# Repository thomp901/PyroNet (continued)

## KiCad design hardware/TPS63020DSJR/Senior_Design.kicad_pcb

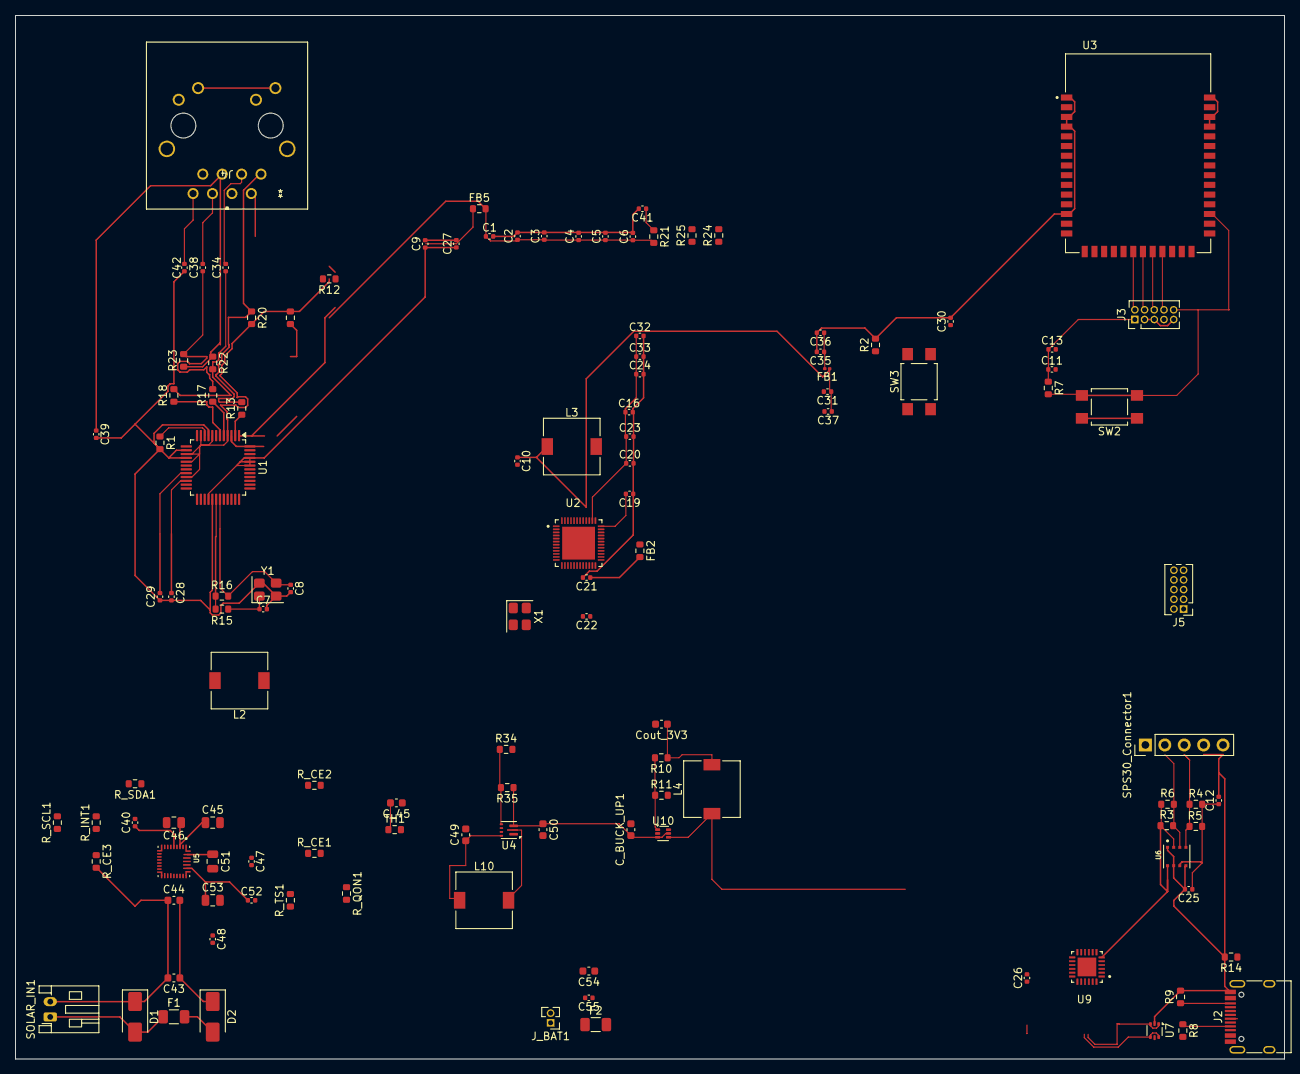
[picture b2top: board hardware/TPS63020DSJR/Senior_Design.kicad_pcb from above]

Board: 2 copper layers, 166.0 x 136.5 mm, 121 parts (0 on the bottom side), 85 nets.

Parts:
C1, C2, C3, C4, C5, C9, C24, C31, C32, C52: 0.1uF; C_0402_1005Metric
C6, C27: 10uF/16V; C_0402_1005Metric
C7, C8: 18pF; C_0402_1005Metric
C10, C26, C29: 4.7uF; C_0402_1005Metric
C11, C12, C21, C25, C30, C36: 100nF; C_0402_1005Metric
C13: 100uF; C_0402_1005Metric
C16: 10uF; C_0402_1005Metric
C19, C23, C33, C37, C40: 1uF; C_0402_1005Metric
C20, C28, C39: 10nF; C_0402_1005Metric
C22, C35: 120pF; C_0402_1005Metric
C34, C38: 6.8nF; C_0402_1005Metric
C41: 22nF; C_0402_1005Metric
C42: 1nF/2kV; C_0402_1005Metric
C43, C49: 10uF; C_0603_1608Metric
C44: 0.1uF; C_0603_1608Metric
C45, C51: 10uF; C_0805_2012Metric
C46: 0.1uF; C_0805_2012Metric
C47, C48: 47 nF; C_0402_1005Metric
C50: 22uF; C_0603_1608Metric
C53: 22uF; C_0805_2012Metric
C54: 10µF; C_0603_1608Metric
C55: 0.1µF; C_0402_1005Metric
C_45: 0.1uF; C_0603_1608Metric
C_BUCK_UP1: 4.7uF; C_0603_1608Metric
Cout_3V3: 22uF; C_0603_1608Metric
D1: D_TVS; D_SMA
D2: D_Schottky; D_SMA
F1: PTC; Fuse_1206_3216Metric
F2: Fuse; Fuse_1206_3216Metric
FB1: BLM03AG700SN1; R_0201_0603Metric
FB2: BLM03PG330SN1; R_0603_1608Metric
FB5: 100R @ 100MHz; R_0603_1608Metric
J2: USB_C_Receptacle_USB2.0_16P; USB_C_Receptacle_HRO_TYPE-C-31-M-12
J3, J5: Conn_ARM_JTAG_SWD_10; PinHeader_2x05_P1.27mm_Vertical
J4: J0011D21BNL; CONN_J0011D21B_PUL
J_BAT1: Conn_01x02; PinHeader_1x02_P1.27mm_Vertical
L2: 2.2 µH; L_7.3x7.3_H3.5
L3: 2.2uH; L_7.3x7.3_H3.5
L4, L10: 1 uH; L_7.3x7.3_H3.5
R1: 12.4K; R_0603_1608Metric
R2: 100; R_0603_1608Metric
R3, R4, R5, R6: 4.7k; R_0603_1608Metric
R7: 10k; R_0603_1608Metric
R8, R9: 5.1k; R_0603_1608Metric
R10: 453K; R_0603_1608Metric
R11, R34: 100k; R_0603_1608Metric
R12, R13, R17, R18: 33R; R_0603_1608Metric
R14, R16: 1M; R_0603_1608Metric
R15: 0R; R_0603_1608Metric
R19, R20, R22, R23: 49.9R; R_0603_1608Metric
R21: 10R; R_0603_1608Metric
R24, R25: 330R; R_0603_1608Metric
R35: 910k; R_0603_1608Metric
R_CE1, R_CE2, R_CE3: 100k; R_0603_1608Metric
R_INT1: 10K; R_0603_1608Metric
R_QON1: 100k; R_0603_1608Metric
R_SCL1: 4.7K; R_0603_1608Metric
R_SDA1: 4.7K; R_0603_1608Metric
R_TS1: 10K; R_0603_1608Metric
SOLAR_IN1: Conn_01x02; JST_PH_S2B-PH-K_1x02_P2.00mm_Horizontal
SPS30_Connector1: Conn_01x05; PinHeader_1x05_P2.54mm_Vertical
SW2, SW3: SW_Push; SW_SPST_TL3305A
TH1: NTC 10k; R_0603_1608Metric
U1: W5500; LQFP-48_7x7mm_P0.5mm
U2: EFR32FG28A122F1024GM48-A; QFN40P600X600X90-49N
U3: BDE-MB1352P71UA32; XCVR_BDE-MB1352P71UA32
U4: TPS61022; Texas_RWU0007A_VQFN-7_2x2mm_P0.5mm
U5: BQ25798RQMR; IC_BQ25798RQMR
U6: BME688; IC_BME688
U7: USBLC6-2P6; SOT-666
U9: CP2102N-A02-GQFN20; QFN50P400X400X80-25N
U10: TLV62569ADRL; SOT-563
X1: Crystal_GND2; Crystal_SMD_3225-4Pin_3.2x2.5mm
Y1: 25MHz; Crystal_SMD_3225-4Pin_3.2x2.5mm

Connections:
5V_VBUS: C45.1, C46.1, J2.A4 (VBUS), J2.A9 (VBUS), J2.B4 (VBUS), J2.B9 (VBUS), U5.2 (VBUS), U5.3 (VBUS), U7.5 (VBUS), U9.7 (VREGIN), U9.8 (VBUS)
+3.3VA: C1.1, C2.1, C3.1, C4.1, C5.1, C6.1, FB5.2, R19.2, R20.2, R21.2, U1.4 (AVDD), U1.8 (AVDD), U1.11 (AVDD), U1.15 (AVDD), U1.17 (AVDD), U1.21 (AVDD)
/26: J5.4 (SWCLK/TCK), U2.26 (PA01)
/27: J5.2 (SWDIO/TMS), U2.27 (PA02)
/28: J5.6 (SWO/TDO), U2.28 (PA03)
/Antenna Module/JTAG_TCKC: J3.4 (SWCLK/TCK), U3.22 (JTAG_TCKC)
/Antenna Module/JTAG_TDI: J3.8 (NC/TDI), U3.24 (DIO_17)
/Antenna Module/JTAG_TDO: J3.6 (SWO/TDO), U3.23 (DIO_16)
/Antenna Module/JTAG_TMSC: J3.2 (SWDIO/TMS), U3.21 (JTAG_TMSC)
/BMS_CE: R_CE3.1, U2.29 (PA04), U5.13 (~CE)
/BMS_INT: R_INT1.1, U2.25 (PA00), U5.21 (~INT)
/DEBUG_UART_RX: U2.34 (PA09), U9.18 (TXD)
/DEBUG_UART_TX: U2.33 (PA08), U9.17 (RXD)
/DECOUPLE: C10.1, C31.1, C37.1, FB1.1, FB2.1, L3.1, U2.40 (DVDD)
/PAVDD: C21.1, C22.1, FB2.2, U2.20 (PAVDD)
/Power/QON: R_QON1.1, U5.12 (~QON)
/Power/REGN: C40.1, R_TS1.1, U5.5 (REGN)
/Power/TS: C_45.2, R_TS1.2, TH1.1, U5.16 (TS)
/Power/VSYS: C49.1, C52.1, C53.1, L10.1, U4.5 (EN), U4.7 (VIN), U5.25 (SYS)
/RFVDD: C35.1, C36.1, FB1.2, U2.14 (RFVDD)
/USBC/D_N: J2.A7 (D-), J2.B7 (D-), U7.1 (I/O1), U7.3 (I/O2), U9.5 (D-)
/USBC/D_P: J2.A6 (D+), J2.B6 (D+), U7.4 (I/O2), U7.6 (I/O1), U9.4 (D+)
/VREGSW: L3.2, U2.37 (VREGSW)
/ethernet/ACTLED: R25.1, U1.27 (ACTLED)
/ethernet/LINKLED: R24.1, U1.25 (LINKLED)
BAT: C54.1, C55.1, F2.1, F2.2, J_BAT1.1, U5.18 (BATP), U5.22 (BAT), U5.23 (BAT)
BDE_RESET: J3.10 (~RESET), R7.2, SW2.2, U2.32 (PA07), U3.30 (~RESET)
BDE_RTS: U2.24 (PB00), U3.19 (DIO_14)
BUCK:3.3V: C9.1, C11.1, C12.1, C13.1, C16.1, C20.1, C23.1, C24.1, C25.1, C26.1, C27.1, C32.1, C33.1, FB5.1, J3.1 (VTref), J4.9, J4.11, J5.1 (VTref), L4.1, R3.1, R4.1, R5.2, R6.1, R7.1, R_INT1.2, R_QON1.2, R_SCL1.2, R_SDA1.2, U1.28 (VDD), U1.43 (PMODE2), U1.44 (PMODE1), U1.45 (PMODE0), U2.38 (VREGVDD), U2.41 (AVDD), U2.42 (IOVDD), U6.2 (CSB), U6.6 (VDDIO), U6.8 (VDD), U9.6 (VDD), U9.9 (RSTB), U10.4 (SW)
BUCK:5V: C50.1, C_BUCK_UP1.1, R35.1, SPS30_Connector1.1, U4.3 (VOUT), U10.3 (VIN), U10.5 (EN)
CS: U1.32 (~SCS), U2.7 (PC06)
DBE_CTS: U2.23 (PB01), U3.20 (DIO_15)
GND: C1.2, C2.2, C3.2, C4.2, C5.2, C6.2, C7.2, C8.2, C9.2, C10.2, C12.2, C16.2, C19.1, C20.2, C21.2, C22.2, C23.2, C24.2, C25.2, C26.2, C27.2, C28.2, C29.2, C30.2, C31.2, C32.2, C33.2, C35.2, C36.2, C37.2, C39.2, C40.2, C41.2, C42.2, C43.2, C44.1, C45.2, C46.2, C49.2, C50.2, C51.2, C52.2, C53.2, C54.2, C55.2, C_45.1, C_BUCK_UP1.2, Cout_3V3.2, D1.1 (A1), J2.A1 (GND), J2.A12 (GND), J2.B1 (GND), J2.B12 (GND), J3.3 (GND), J3.5 (GND), J3.9 (GNDDetect), J5.3 (GND), J5.5 (GND), J5.9 (GNDDetect), J_BAT1.2, R1.2, R2.2, R8.2, R9.2, R11.2, R14.2, R34.2, R_CE1.2, R_CE2.2, R_CE3.2, SOLAR_IN1.2, SPS30_Connector1.4, SPS30_Connector1.5, SW2.1, TH1.2, U1.3 (AGND), U1.9 (AGND), U1.14 (AGND), U1.16 (AGND), U1.19 (AGND), U1.29 (GND), U1.48 (AGND), U2.49 (VSS), U3.1 (GND), U3.3 (GND), U3.4 (GND), U3.13 (GND), U3.39 (GND), U3.40 (GND), U3.42 (GND), U4.1 (GND), U4.6 (MODE), U5.27 (GND), U6.1 (GND), U6.5 (SDO), U6.7 (GND__1), U7.2 (GND), U9.3 (GND), U9.12 (GND), U9.21 (EPAD), U10.2 (GND), X1.2, Y1.2 (G), Y1.4 (G)
INT: U1.36 (~INT), U2.8 (PC07)
MCU_RX_BDE_TX: U2.31 (PA06), U3.18 (DIO_13)
MCU_TX_BDE_RX: U2.30 (PA05), U3.17 (DIO_12)
unnamed: C7.1, R15.2, Y1.1
unnamed: C34.1, R18.2, R22.2
unnamed: C34.2, J4.3
unnamed: C38.1, R17.2, R23.2
unnamed: C38.2, J4.6
unnamed: C39.1, J4.5, R22.1, R23.1
unnamed: C41.1, J4.4, R21.1
unnamed: C42.1, J4.8
unnamed: Cout_3V3.1, L4.2, R10.1
unnamed: D1.2 (A2), F1.1, SOLAR_IN1.1
unnamed: D2.2 (A), F1.2
unnamed: C43.1, C44.2, D2.1 (K), U5.9 (VAC1)
unnamed: J2.A5 (CC1), R8.1
unnamed: J2.B5 (CC2), R9.1
unnamed: J2.S1 (SHIELD), R14.1
unnamed: J4.1, R13.2, R20.1
unnamed: J4.2, R12.2, R19.1
unnamed: J4.10, R24.2
unnamed: J4.12, R25.2
unnamed: R2.1, SW3.1
unnamed: C28.1, U1.22 (1V2O)
unnamed: R1.1, U1.10 (EXRES1)
unnamed: R17.1, U1.5 (RXN)
unnamed: R18.1, U1.6 (RXP)
unnamed: C29.1, U1.20 (TOCAP)
unnamed: R12.1, U1.1 (TXN)
unnamed: R13.1, U1.2 (TXP)
unnamed: R15.1, R16.1, U1.30 (XI/CLKIN)
unnamed: C8.1, R16.2, U1.31 (XO), Y1.3
unnamed: C19.2, U2.36 (DECOUPLE)
unnamed: U2.11 (HFXTAL_I), X1.1
unnamed: U2.12 (HFXTAL_O), X1.3
unnamed: R34.1, R35.2, U4.4 (FB)
unnamed: L10.2, U4.2 (SW)
unnamed: C47.1, U5.4 (BTST1)
unnamed: C48.2, U5.19 (BTST2)
unnamed: R_CE1.1, U5.17 (ILIM_HIZ)
unnamed: C51.1, U5.29 (PMID)
unnamed: R_CE2.1, U5.20 (PROG)
unnamed: C47.2, L2.2, U5.28 (SW1)
unnamed: C48.1, L2.1, U5.26 (SW2)
unnamed: R10.2, R11.1, U10.1 (FB)
RESET: C30.1, J5.10 (~RESET), SW3.2, U2.13 (~RESET)
SCL: R4.2, R5.1, R_SCL1.1, SPS30_Connector1.3, U2.2 (PC01), U5.14 (SCL), U6.4 (SCK)
SDA: R3.2, R6.2, R_SDA1.1, SPS30_Connector1.2, U2.3 (PC02), U5.15 (SDA), U6.3 (SDI)
SPI_MISO: U1.34 (MISO), U2.6 (PC05)
SPI_MOSI: U1.35 (MOSI), U2.5 (PC04)
SPI_SCK: U1.33 (SCLK), U2.4 (PC03)
VDD: C11.2, C13.2, U3.14 (VDD), U3.15 (VDD)

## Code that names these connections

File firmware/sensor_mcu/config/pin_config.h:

#ifndef PIN_CONFIG_H
#define PIN_CONFIG_H

#include "sl_gpio.h"

// $[CMU]
// [CMU]$

// $[LFXO]
// [LFXO]$

// $[PRS.ASYNCH0]
// [PRS.ASYNCH0]$

// $[PRS.ASYNCH1]
// [PRS.ASYNCH1]$

// $[PRS.ASYNCH2]
// [PRS.ASYNCH2]$

// $[PRS.ASYNCH3]
// [PRS.ASYNCH3]$

// $[PRS.ASYNCH4]
// [PRS.ASYNCH4]$

// $[PRS.ASYNCH5]
// [PRS.ASYNCH5]$

// $[PRS.ASYNCH6]
// [PRS.ASYNCH6]$

// $[PRS.ASYNCH7]
// [PRS.ASYNCH7]$

// $[PRS.ASYNCH8]
// [PRS.ASYNCH8]$

// $[PRS.ASYNCH9]
// [PRS.ASYNCH9]$

// $[PRS.ASYNCH10]
// [PRS.ASYNCH10]$

// $[PRS.ASYNCH11]
// [PRS.ASYNCH11]$

// $[PRS.SYNCH0]
// [PRS.SYNCH0]$

// $[PRS.SYNCH1]
// [PRS.SYNCH1]$

// $[PRS.SYNCH2]
// [PRS.SYNCH2]$

// $[PRS.SYNCH3]
// [PRS.SYNCH3]$

// $[GPIO]
// [GPIO]$

// $[TIMER0]
// [TIMER0]$

// $[TIMER1]
// [TIMER1]$

// $[TIMER2]
// [TIMER2]$

// $[TIMER3]
// [TIMER3]$

// $[TIMER4]
// [TIMER4]$

// $[USART0]
// [USART0]$

// $[I2C1]
// [I2C1]$

// $[EUSART1]
// [EUSART1]$

// $[EUSART2]
// [EUSART2]$

// $[LCD]
// [LCD]$

// $[KEYSCAN]
// [KEYSCAN]$

// $[LETIMER0]
// [LETIMER0]$

// $[IADC0]
// [IADC0]$

// $[ACMP0]
// [ACMP0]$

// $[ACMP1]
// [ACMP1]$

// $[VDAC0]
// [VDAC0]$

// $[PCNT0]
// [PCNT0]$

// $[LESENSE]
// [LESENSE]$

// $[I2C0]
// [I2C0]$

// $[EUSART0]
// [EUSART0]$

// $[PTI]
// [PTI]$

// $[MODEM]
// [MODEM]$

// $[CUSTOM_PIN_NAME]
#ifndef _PORT                                   
#define _PORT                                    SL_GPIO_PORT_A
#endif
#ifndef _PIN                                    
#define _PIN                                     0
#endif

// <<< sl:start pin_tool >>>
// <i2c signal=SCL,SDA> SL_I2C_BUS
// I2C1 on PD02/PD03
#define SL_I2C_BUS_PERIPHERAL                    I2C1
#define SL_I2C_BUS_PERIPHERAL_NO                 1
#define SL_I2C_BUS_CLOCK                        cmuClock_I2C1

// I2C1 SCL on PD02
#define SL_I2C_BUS_SCL_PORT                      SL_GPIO_PORT_D
#define SL_I2C_BUS_SCL_PIN                       2

// I2C1 SDA on PD03
#define SL_I2C_BUS_SDA_PORT                      SL_GPIO_PORT_D
#define SL_I2C_BUS_SDA_PIN                       3

// <gpio> DEBUG_LED_D103
// D103 on PA07
#define DEBUG_LED_D103_PORT                      SL_GPIO_PORT_A
#define DEBUG_LED_D103_PIN                       7

// <gpio> DEBUG_LED_D102
// D102 on PA08
#define DEBUG_LED_D102_PORT                      SL_GPIO_PORT_A
#define DEBUG_LED_D102_PIN                       8

// <gpio> DEBUG_LED_D101
// D101 on PA09
#define DEBUG_LED_D101_PORT                      SL_GPIO_PORT_A
#define DEBUG_LED_D101_PIN                       9
// <<< sl:end pin_tool >>>































// [CUSTOM_PIN_NAME]$


#endif // PIN_CONFIG_H

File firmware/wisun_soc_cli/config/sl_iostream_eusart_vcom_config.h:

/***************************************************************************//**
 * @file
 * @brief IOSTREAM_EUSART Config.
 *******************************************************************************
 * # License
 * <b>Copyright 2020 Silicon Laboratories Inc. www.silabs.com</b>
 *******************************************************************************
 *
 * SPDX-License-Identifier: Zlib
 *
 * The licensor of this software is Silicon Laboratories Inc.
 *
 * This software is provided 'as-is', without any express or implied
 * warranty. In no event will the authors be held liable for any damages
 * arising from the use of this software.
 *
 * Permission is granted to anyone to use this software for any purpose,
 * including commercial applications, and to alter it and redistribute it
 * freely, subject to the following restrictions:
 *
 * 1. The origin of this software must not be misrepresented; you must not
 *    claim that you wrote the original software. If you use this software
 *    in a product, an acknowledgment in the product documentation would be
 *    appreciated but is not required.
 * 2. Altered source versions must be plainly marked as such, and must not be
 *    misrepresented as being the original software.
 * 3. This notice may not be removed or altered from any source distribution.
 *
 ******************************************************************************/

#ifndef SL_IOSTREAM_EUSART_VCOM_CONFIG_H
#define SL_IOSTREAM_EUSART_VCOM_CONFIG_H

// <<< Use Configuration Wizard in Context Menu >>>

// <h>EUART settings

// <q SL_IOSTREAM_EUSART_VCOM_ENABLE_HIGH_FREQUENCY> Enable High frequency mode
// <i> Default: 1
#define SL_IOSTREAM_EUSART_VCOM_ENABLE_HIGH_FREQUENCY        1

// <o SL_IOSTREAM_EUSART_VCOM_BAUDRATE> Baud rate
// <i> Default: 115200
#define SL_IOSTREAM_EUSART_VCOM_BAUDRATE              115200

// <o SL_IOSTREAM_EUSART_VCOM_PARITY> Parity mode to use
// <SL_IOSTREAM_EUSART_UART_NO_PARITY=> No Parity
// <SL_IOSTREAM_EUSART_UART_EVEN_PARITY=> Even parity
// <SL_IOSTREAM_EUSART_UART_ODD_PARITY=> Odd parity
// <i> Default: SL_IOSTREAM_EUSART_UART_NO_PARITY
#define SL_IOSTREAM_EUSART_VCOM_PARITY                SL_IOSTREAM_EUSART_UART_NO_PARITY

// <o SL_IOSTREAM_EUSART_VCOM_STOP_BITS> Number of stop bits to use.
// <SL_IOSTREAM_EUSART_UART_STOP_BITS_0P5=> 0.5 stop bits
// <SL_IOSTREAM_EUSART_UART_STOP_BITS_1=> 1 stop bits
// <SL_IOSTREAM_EUSART_UART_STOP_BITS_1P5=> 1.5 stop bits
// <SL_IOSTREAM_EUSART_UART_STOP_BITS_2=> 2 stop bits
// <i> Default: SL_IOSTREAM_EUSART_UART_STOP_BITS_1
#define SL_IOSTREAM_EUSART_VCOM_STOP_BITS             SL_IOSTREAM_EUSART_UART_STOP_BITS_1

// <o SL_IOSTREAM_EUSART_VCOM_FLOW_CONTROL_TYPE> Flow control
// <SL_IOSTREAM_EUSART_UART_FLOW_CTRL_NONE=> None
// <SL_IOSTREAM_EUSART_UART_FLOW_CTRL_CTS=> CTS
// <SL_IOSTREAM_EUSART_UART_FLOW_CTRL_RTS=> RTS
// <SL_IOSTREAM_EUSART_UART_FLOW_CTRL_CTS_RTS=> CTS/RTS
// <SL_IOSTREAM_EUSART_UART_FLOW_CTRL_SOFT=> Software Flow control (XON/XOFF)
// <i> Default: SL_IOSTREAM_EUSART_UART_FLOW_CTRL_NONE
#define SL_IOSTREAM_EUSART_VCOM_FLOW_CONTROL_TYPE     SL_IOSTREAM_EUSART_UART_FLOW_CTRL_NONE

// <o SL_IOSTREAM_EUSART_VCOM_RX_BUFFER_SIZE> Receive buffer size
// <i> Default: 32
#define SL_IOSTREAM_EUSART_VCOM_RX_BUFFER_SIZE    128

// <q SL_IOSTREAM_EUSART_VCOM_CONVERT_BY_DEFAULT_LF_TO_CRLF> Convert \n to \r\n
// <i> It can be changed at runtime using the C API.
// <i> Default: 0
#define SL_IOSTREAM_EUSART_VCOM_CONVERT_BY_DEFAULT_LF_TO_CRLF     true

// <q SL_IOSTREAM_EUSART_VCOM_RESTRICT_ENERGY_MODE_TO_ALLOW_RECEPTION> Restrict the energy mode to allow the reception.
// <i> Default: 1
// <i> Limits the lowest energy mode the system can sleep to in order to keep the reception on. May cause higher power consumption.
#define SL_IOSTREAM_EUSART_VCOM_RESTRICT_ENERGY_MODE_TO_ALLOW_RECEPTION    1

// </h>

// <<< end of configuration section >>>

// <<< sl:start pin_tool >>>
// <eusart signal=TX,RX,(CTS),(RTS)> SL_IOSTREAM_EUSART_VCOM
// $[EUSART_SL_IOSTREAM_EUSART_VCOM]
#define SL_IOSTREAM_EUSART_VCOM_PERIPHERAL       EUSART0
#define SL_IOSTREAM_EUSART_VCOM_PERIPHERAL_NO    0

// EUSART0 TX on PA08
#define SL_IOSTREAM_EUSART_VCOM_TX_PORT          SL_GPIO_PORT_A
#define SL_IOSTREAM_EUSART_VCOM_TX_PIN           8

// EUSART0 RX on PA09
#define SL_IOSTREAM_EUSART_VCOM_RX_PORT          SL_GPIO_PORT_A
#define SL_IOSTREAM_EUSART_VCOM_RX_PIN           9

// EUSART0 CTS on PA10
#define SL_IOSTREAM_EUSART_VCOM_CTS_PORT         SL_GPIO_PORT_A
#define SL_IOSTREAM_EUSART_VCOM_CTS_PIN          10

// EUSART0 RTS on PA00
#define SL_IOSTREAM_EUSART_VCOM_RTS_PORT         SL_GPIO_PORT_A
#define SL_IOSTREAM_EUSART_VCOM_RTS_PIN          0

// [EUSART_SL_IOSTREAM_EUSART_VCOM]$
// <<< sl:end pin_tool >>>

#endif

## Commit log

2026-02-22 Initial git commit
2026-02-22 Update README.md with Hardware
2026-02-27 simple changes to the Pulse leds
2026-02-28 usbc-update
2026-03-01 Debugging LED added
2026-03-03 Intergrated 3.3V BuckBoost and 5V Boost
2026-03-03 Added thermistor connection
2026-03-03 Added LF crystal
2026-03-03 Unified I2C pull-ups to MCU page
2026-03-03 RFVDD/PAVDD wip
2026-03-03 removed Ethernet LED diodes
2026-03-03 MCU Reset Pin fix
2026-03-03 test
2026-03-03 MCU Capacitor Updates
2026-03-04 Fixed MCU JTAG/Reordered pages
2026-03-04 Fixed MCU power pins
2026-03-04 BDE JTAG pullup
2026-03-04 cleanup
2026-03-04 Replaced 3.3V symbol
2026-03-05 deleted unsused files/folders
2026-03-05 added footprint/symbols
2026-03-05 updated major symbol and footprints
2026-03-05 added 3dmodels
2026-03-05 updated 5V power and pin
2026-03-05 passing ERC w/ exclusions
2026-03-05 updated annotations
2026-03-06 added ship fet
2026-03-06 footprint update
2026-03-06 footprint update 2
2026-03-06 PCB_Layout_240
2026-03-06 layout_246
2026-03-06 updated ESD/Inductor footprints
2026-03-06 pcb_update_1232
2026-03-06 kam_1237
2026-03-06 Buck/Bost layouts and part of BMS
2026-03-06 updated footprints
2026-03-07 updated labels
2026-03-07 fixed ERC issues
2026-03-07 reannotate
2026-03-07 updated JTAG ESD protection
2026-03-07 added QON pushbutton
2026-03-07 PCB footprint update
2026-03-07 BDE footprint/new 5V boost
2026-03-08 PCB_1934_Mar8
2026-03-08 BME/BDE pin update
2026-03-09 PCB_1149_Mar9
2026-03-09 PCB_1356_Mar9
2026-03-09 MCU pin reassignment
2026-03-09 MCU pin update
2026-03-09 moved layout
2026-03-10 ethernet layout
2026-03-10 PCB_layout_2327_Mar9
2026-03-10 BMS layout
2026-03-10 PCB_layout_1239_Mar10
2026-03-10 ethernet/wisun pcb update
2026-03-10 PCB WIP
2026-03-11 PCB_layout_2225_Mar10
2026-03-11 Power Layout WIP
2026-03-11 PCB_layout_1215_Mar11
2026-03-11 5VB PCB layout
2026-03-11 PCB layout update
2026-03-11 BDE JTAG layout
2026-03-11 ethernet cap layout
2026-03-12 PCB_layout_957pm_Mar11
2026-03-12 PCB update
2026-03-13 added data sheet and added some of the vias the PCB design
2026-03-13 PCB Layout - Rev 1.0
2026-03-13 Added Mounting Holes
2026-03-13 moved mounting holes
2026-03-13 minor fix
2026-03-13 USB move
2026-03-13 3dmodels update
2026-03-13 silkscreen update
2026-03-13 readded mounting holes
2026-03-13 3.3V via fix
2026-03-13 3dmodel fix
2026-03-13 review changes/USB next
2026-03-14 USB update
2026-03-14 deleted unused assets
2026-03-14 Rev 1.2 - debuggin pins added
2026-03-14 Correction: Rev 1.1
2026-03-15 PCB cleanup
2026-03-15 no blind/buried vias
2026-03-16 advancedpcb contstraints
2026-03-16 minor updates
2026-03-17 minor fixes
2026-03-17 PCBWay submission
2026-04-03 label cleanup
2026-04-08 values subbed
2026-04-13 csp added
2026-04-13 csp update
2026-04-13 Convert csp from submodule to regular folder
2026-04-14 sql update
2026-04-14 firmware starter code
2026-04-14 csp rework
2026-04-15 node page wip
2026-04-15 node page update
2026-04-15 full csp update
2026-04-15 csp minor updates
2026-04-16 RCP starter
2026-04-16 stack update
2026-04-17 debug LED test - working
2026-04-17 clean slate
2026-04-17 SWO debug reads
2026-04-17 bme/bsec integrated
2026-04-18 pm2.5 sensor working
2026-04-18 feat: add packet ingest pipeline and Postgres persistence
2026-04-18 ncp starter
2026-04-20 value update
2026-04-21 restart - SWO working
2026-04-21 Wi-SUN join working
2026-04-21 empty starter
2026-04-21 makefile re-created
2026-04-21 sync sensor_mcu directory
2026-04-21 firmware update
2026-04-21 sps30 files added
2026-04-21 SWO rework / UART wip
2026-04-21 I2C WIP
2026-04-21 UART update
2026-04-21 SWO update
2026-04-21 gitignore added
2026-04-22 bme update
2026-04-22 sps30 update
2026-04-22 risk_logic
2026-04-22 mcu/ncp link started
2026-04-22 mcu/ncp link
2026-04-22 notifications
2026-04-22 notif
2026-04-22 cleanup: remove generated files
2026-04-22 gateway update
2026-04-23 ingestion API update
2026-04-23 API WIP
2026-04-23 NCP handshaking
2026-04-23 NCP handshake
2026-04-23 initial gateway commit
2026-04-23 gateway clean
2026-04-23 connecting to Wi-SUN agian
2026-04-24 voc persist update
2026-04-24 downlink working
2026-04-24 config tests
2026-04-24 Add PyroNet CSP spoof packet CLI
2026-04-24 links update
2026-04-24 fault handler
2026-04-24 email updates
2026-04-24 bug solved
2026-04-24 neighbor update
2026-04-24 working spoof device
2026-04-24 reset/survives br reset
2026-04-24 400x stronger signal
2026-04-24 parent update
2026-04-24 demo
